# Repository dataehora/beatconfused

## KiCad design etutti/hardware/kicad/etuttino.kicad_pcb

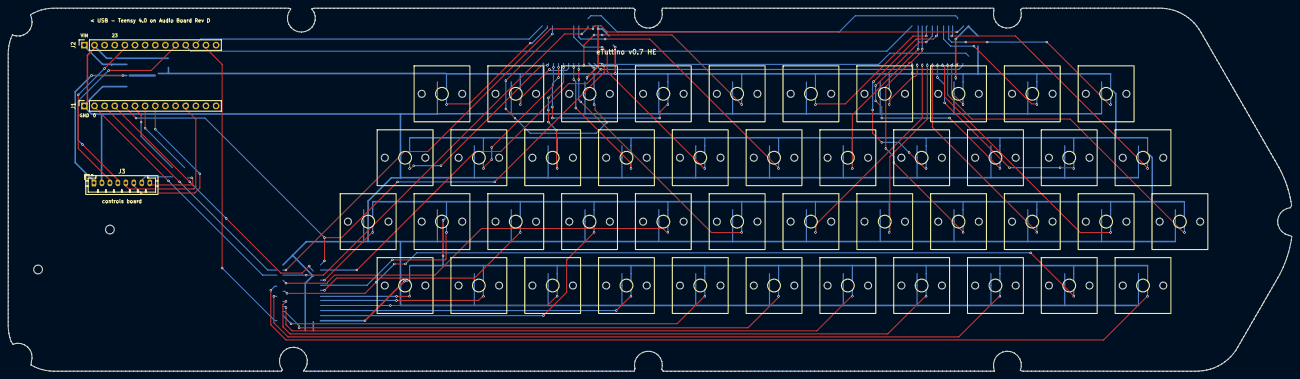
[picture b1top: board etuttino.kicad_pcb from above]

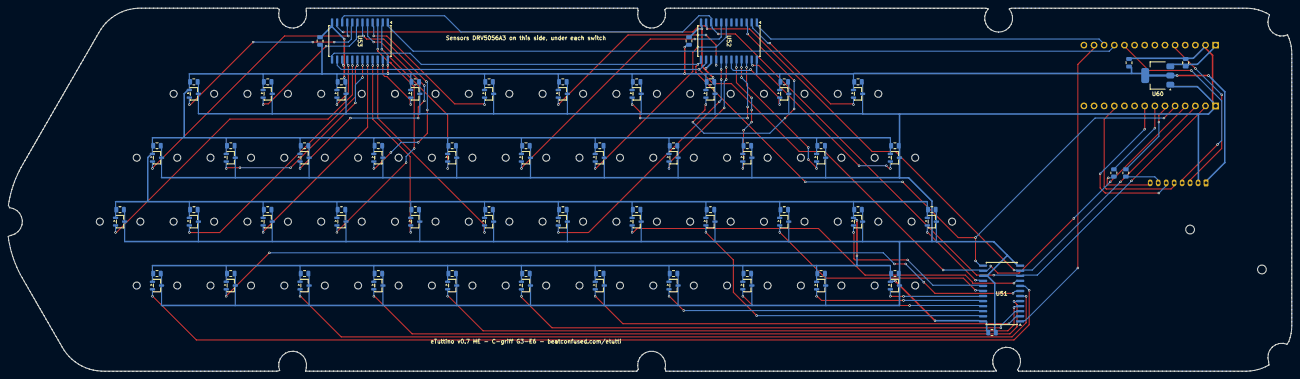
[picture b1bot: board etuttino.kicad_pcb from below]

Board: 2 copper layers, 321.8 x 91.0 mm, 148 parts (99 on the bottom side), 62 nets.

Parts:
C1, C2, C3, C4, C5, C6, C7, C8, C9, C10, C11, C12, C13, C14, C15, C16, C17, C18, C19, C20, C21, C22, C23, C24, C25, C26, C27, C28, C29, C30, C31, C32, C33, C34, C35, C36, C37, C38, C39, C40, C41, C42, C43, C44, C71, C72, C73: 100nF; C_0805_2012Metric
C80: 10uF; C_0805_2012Metric
C81: 22uF; C_0805_2012Metric
H1, H2: MountingHole_2.2mm_M2
J1, J2: PinSocket_1x14_P2.54mm_Vertical
J3: controls board; JST_PH_B8B-PH-K_1x08_P2.00mm_Vertical
R1, R2: 330; R_0805_2012Metric
SW1, SW2, SW3, SW4, SW5, SW6, SW7, SW8, SW9, SW10, SW11, SW12, SW13, SW14, SW15, SW16, SW17, SW18, SW19, SW20, SW21, SW22, SW23, SW24, SW25, SW26, SW27, SW28, SW29, SW30, SW31, SW32, SW33, SW34, SW35, SW36, SW37, SW38, SW39, SW40, SW41, SW42, SW43, SW44: Gateron_Magnetic_MX_1u
U1, U2, U3, U4, U5, U6, U7, U8, U9, U10, U11, U12, U13, U14, U15, U16, U17, U18, U19, U20, U21, U22, U23, U24, U25, U26, U27, U28, U29, U30, U31, U32, U33, U34, U35, U36, U37, U38, U39, U40, U41, U42, U43, U44: DRV5056A3QDBZR; SOT-23-3
U51, U52, U53: CD74HC4067M96; SOIC-24W_7.5x15.4mm_P1.27mm
U60: AMS1117-3.3; SOT-223-3_TabPin2

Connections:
COM0: J2.13, U51.1
COM1: J2.12, U52.1
COM2: J2.11, U53.1
ENC_A: J2.10, J3.4
ENC_B: J1.11, J3.5
ENC_SW: J1.8, J3.6
GND: C1.2, C2.2, C3.2, C4.2, C5.2, C6.2, C7.2, C8.2, C9.2, C10.2, C11.2, C12.2, C13.2, C14.2, C15.2, C16.2, C17.2, C18.2, C19.2, C20.2, C21.2, C22.2, C23.2, C24.2, C25.2, C26.2, C27.2, C28.2, C29.2, C30.2, C31.2, C32.2, C33.2, C34.2, C35.2, C36.2, C37.2, C38.2, C39.2, C40.2, C41.2, C42.2, C43.2, C44.2, C71.2, C72.1, C73.1, C80.1, C81.1, J1.1, J2.2, J3.2, U1.3, U2.3, U3.3, U4.3, U5.3, U6.3, U7.3, U8.3, U9.3, U10.3, U11.3, U12.3, U13.3, U14.3, U15.3, U16.3, U17.3, U18.3, U19.3, U20.3, U21.3, U22.3, U23.3, U24.3, U25.3, U26.3, U27.3, U28.3, U29.3, U30.3, U31.3, U32.3, U33.3, U34.3, U35.3, U36.3, U37.3, U38.3, U39.3, U40.3, U41.3, U42.3, U43.3, U44.3, U51.12, U51.15, U52.12, U52.15, U53.12, U53.15, U60.1
LED_G: J3.8, R2.2
LED_G_DRV: J1.7, R2.1
LED_R: J3.7, R1.2
LED_R_DRV: J1.6, R1.1
OUT_U1: U1.2, U51.19
OUT_U2: U2.2, U51.20
OUT_U3: U3.2, U51.21
OUT_U4: U4.2, U51.22
OUT_U5: U5.2, U51.2
OUT_U6: U6.2, U51.3
OUT_U7: U7.2, U51.4
OUT_U8: U8.2, U51.5
OUT_U9: U9.2, U51.6
OUT_U10: U10.2, U51.7
OUT_U11: U11.2, U51.8
OUT_U12: U12.2, U51.16
OUT_U13: U13.2, U51.17
OUT_U14: U14.2, U51.18
OUT_U15: U15.2, U51.23
OUT_U16: U16.2, U51.9
OUT_U17: U17.2, U52.17
OUT_U18: U18.2, U53.22
OUT_U19: U19.2, U53.21
OUT_U20: U20.2, U53.3
OUT_U21: U21.2, U53.20
OUT_U22: U22.2, U53.18
OUT_U23: U23.2, U53.17
OUT_U24: U24.2, U52.23
OUT_U25: U25.2, U52.22
OUT_U26: U26.2, U52.20
OUT_U27: U27.2, U52.18
OUT_U28: U28.2, U52.7
OUT_U29: U29.2, U52.8
OUT_U30: U30.2, U53.2
OUT_U31: U31.2, U53.6
OUT_U32: U32.2, U53.5
OUT_U33: U33.2, U53.19
OUT_U34: U34.2, U53.9
OUT_U35: U35.2, U52.2
OUT_U36: U36.2, U52.19
OUT_U37: U37.2, U52.3
OUT_U38: U38.2, U52.21
OUT_U39: U39.2, U52.16
OUT_U40: U40.2, U53.4
OUT_U41: U41.2, U53.23
OUT_U42: U42.2, U53.16
OUT_U43: U43.2, U53.7
OUT_U44: U44.2, U53.8
POT: J2.5, J3.3
SEL0: J1.2, U51.10, U52.10, U53.10
SEL1: J1.3, U51.11, U52.11, U53.11
SEL2: J1.4, U51.14, U52.14, U53.14
SEL3: J1.5, U51.13, U52.13, U53.13
VCC: C1.1, C2.1, C3.1, C4.1, C5.1, C6.1, C7.1, C8.1, C9.1, C10.1, C11.1, C12.1, C13.1, C14.1, C15.1, C16.1, C17.1, C18.1, C19.1, C20.1, C21.1, C22.1, C23.1, C24.1, C25.1, C26.1, C27.1, C28.1, C29.1, C30.1, C31.1, C32.1, C33.1, C34.1, C35.1, C36.1, C37.1, C38.1, C39.1, C40.1, C41.1, C42.1, C43.1, C44.1, C71.1, C72.2, C73.2, C81.2, J3.1, U1.1, U2.1, U3.1, U4.1, U5.1, U6.1, U7.1, U8.1, U9.1, U10.1, U11.1, U12.1, U13.1, U14.1, U15.1, U16.1, U17.1, U18.1, U19.1, U20.1, U21.1, U22.1, U23.1, U24.1, U25.1, U26.1, U27.1, U28.1, U29.1, U30.1, U31.1, U32.1, U33.1, U34.1, U35.1, U36.1, U37.1, U38.1, U39.1, U40.1, U41.1, U42.1, U43.1, U44.1, U51.24, U52.24, U53.24, U60.2
VIN: C80.2, J2.1, U60.3

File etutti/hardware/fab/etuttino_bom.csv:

Comment,Designator,Footprint,LCSC Part #
"DRV5056A3QDBZR","U1,U2,U3,U4,U5,U6,U7,U8,U9,U10,U11,U12,U13,U14,U15,U16,U17,U18,U19,U20,U21,U22,U23,U24,U25,U26,U27,U28,U29,U30,U31,U32,U33,U34,U35,U36,U37,U38,U39,U40,U41,U42,U43,U44","SOT-23-3",""
"100nF 0805 X7R","C1,C2,C3,C4,C5,C6,C7,C8,C9,C10,C11,C12,C13,C14,C15,C16,C17,C18,C19,C20,C21,C22,C23,C24,C25,C26,C27,C28,C29,C30,C31,C32,C33,C34,C35,C36,C37,C38,C39,C40,C41,C42,C43,C44,C71,C72,C73","C_0805","C49678"
"CD74HC4067M96","U51,U52,U53","SOIC-24W",""
"AMS1117-3.3","U60","SOT-223","C6186"
"10uF 0805","C80","C_0805","C15850"
"22uF 0805","C81","C_0805","C45783"
"330R 0805","R1,R2","R_0805","C17630"

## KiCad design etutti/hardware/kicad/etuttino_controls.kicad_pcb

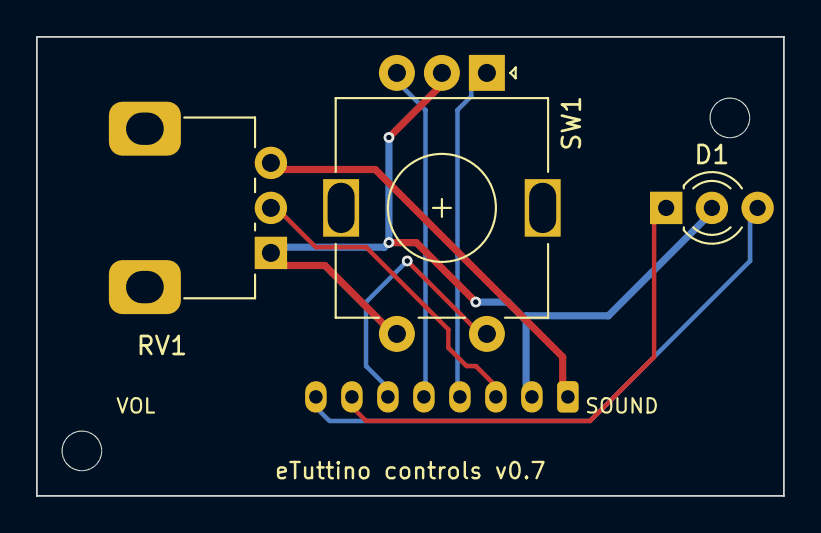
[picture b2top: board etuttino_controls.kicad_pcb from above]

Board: 2 copper layers, 41.5 x 25.5 mm, 6 parts (1 on the bottom side), 8 nets.

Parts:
D1: LED 3mm R/G CC; LED_D3.0mm-3
H1, H2: MountingHole_2.2mm_M2
J1: to main board J3; JST_PH_B8B-PH-K_1x08_P2.00mm_Vertical
RV1: RK09K 10k lin; Potentiometer_Alps_RK09K_Single_Vertical
SW1: EC11E; RotaryEncoder_Alps_EC11E-Switch_Vertical_H20mm

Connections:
ENC_A: J1.4, SW1.A
ENC_B: J1.5, SW1.B
ENC_SW: J1.6, SW1.S2
GND: D1.2, J1.2, RV1.1, SW1.C, SW1.S1
LED_G: D1.3, J1.8
LED_R: D1.1, J1.7
POT: J1.3, RV1.2
VCC: J1.1, RV1.3

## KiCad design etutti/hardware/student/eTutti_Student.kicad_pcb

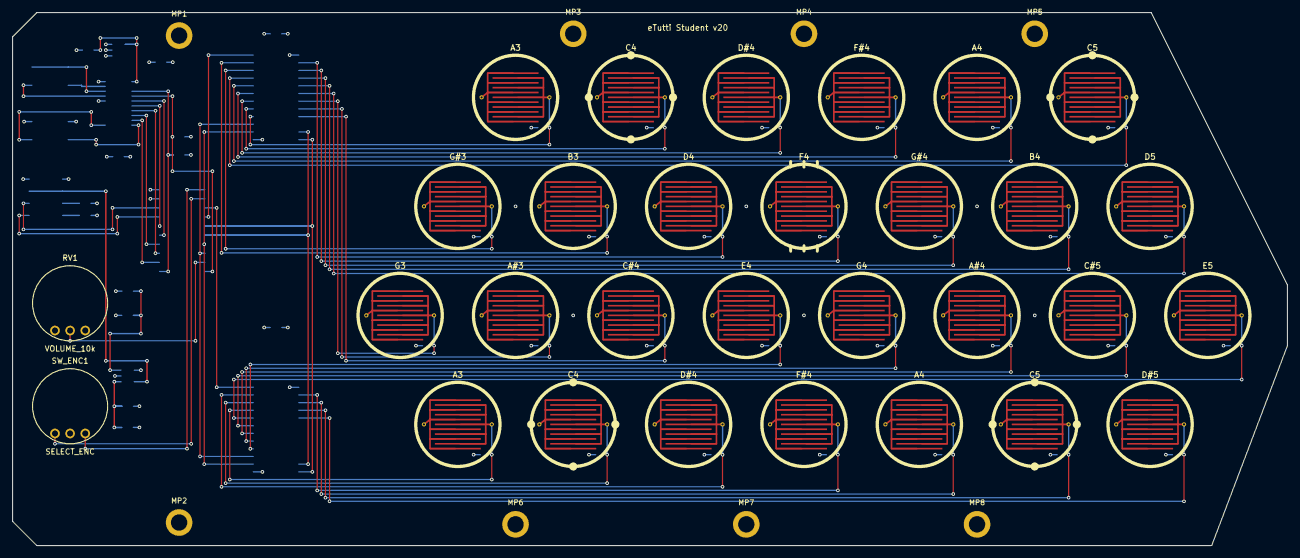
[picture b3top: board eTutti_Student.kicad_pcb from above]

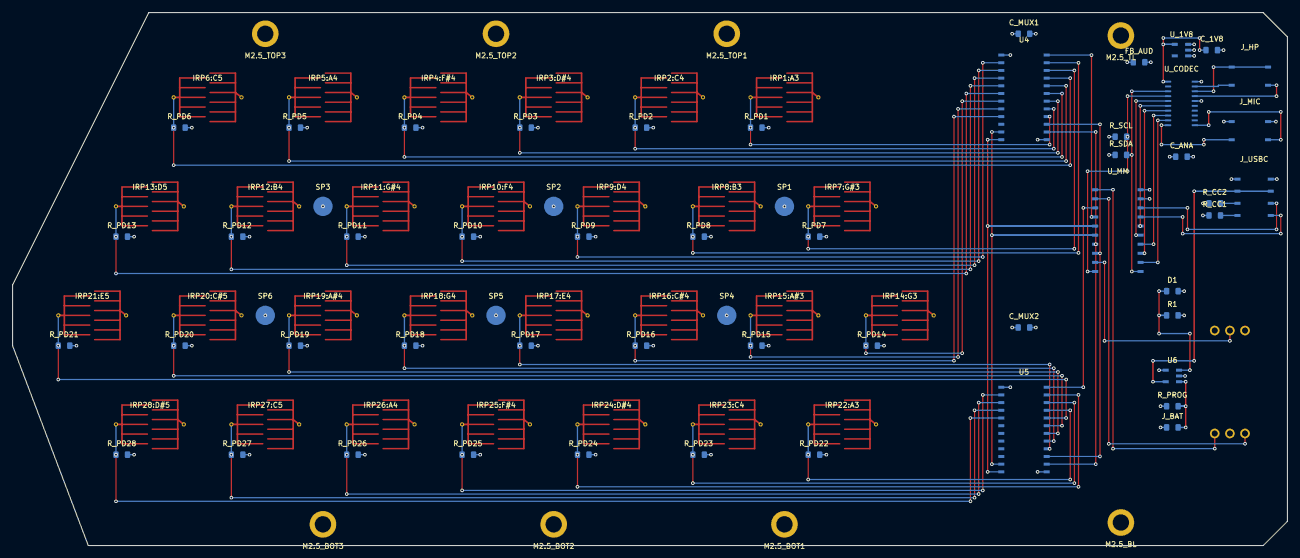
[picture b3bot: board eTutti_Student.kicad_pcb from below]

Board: 4 copper layers, 210.5 x 88.0 mm, 94 parts (56 on the bottom side), 60 nets.

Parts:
C_1V8: 100nF; SMD_0805_C_1V8
C_ANA: 10uF; SMD_0805_C_ANA
C_MUX1: 100nF; SMD_0805_C_MUX1
C_MUX2: 100nF; SMD_0805_C_MUX2
D1: LED_STATUS; SMD_0805_D1
FB_AUD: FERRITE; SMD_0805_FB_AUD
IRP1, IRP22: A3; IRP_14mm_Tactile
IRP2, IRP23: C4; IRP_14mm_Tactile
IRP3, IRP24: D#4; IRP_14mm_Tactile
IRP4, IRP25: F#4; IRP_14mm_Tactile
IRP5, IRP26: A4; IRP_14mm_Tactile
IRP6, IRP27: C5; IRP_14mm_Tactile
IRP7: G#3; IRP_14mm_Tactile
IRP8: B3; IRP_14mm_Tactile
IRP9: D4; IRP_14mm_Tactile
IRP10: F4; IRP_14mm_Tactile
IRP11: G#4; IRP_14mm_Tactile
IRP12: B4; IRP_14mm_Tactile
IRP13: D5; IRP_14mm_Tactile
IRP14: G3; IRP_14mm_Tactile
IRP15: A#3; IRP_14mm_Tactile
IRP16: C#4; IRP_14mm_Tactile
IRP17: E4; IRP_14mm_Tactile
IRP18: G4; IRP_14mm_Tactile
IRP19: A#4; IRP_14mm_Tactile
IRP20: C#5; IRP_14mm_Tactile
IRP21: E5; IRP_14mm_Tactile
IRP28: D#5; IRP_14mm_Tactile
J_BAT: BATT_JST; SMD_0805_J_BAT
J_HP: PHONES_3.5mm; J_HP_Back
J_MIC: MIC_IN_3.5mm; J_MIC_Back
J_USBC: USB-C_PORT; J_USBC_Back
MP1: M2.5_TL; MountingHole_M2.5_Pad
MP2: M2.5_BL; MountingHole_M2.5_Pad
MP3: M2.5_TOP1; MountingHole_M2.5_Pad
MP4: M2.5_TOP2; MountingHole_M2.5_Pad
MP5: M2.5_TOP3; MountingHole_M2.5_Pad
MP6: M2.5_BOT1; MountingHole_M2.5_Pad
MP7: M2.5_BOT2; MountingHole_M2.5_Pad
MP8: M2.5_BOT3; MountingHole_M2.5_Pad
R1: 330R; SMD_0805_R1
RV1: VOLUME_10k; RV1_Top
R_CC1: 5.1k; SMD_0805_R_CC1
R_CC2: 5.1k; SMD_0805_R_CC2
R_PD1: 10k; SMD_0805_R_PD1
R_PD2: 10k; SMD_0805_R_PD2
R_PD3: 10k; SMD_0805_R_PD3
R_PD4: 10k; SMD_0805_R_PD4
R_PD5: 10k; SMD_0805_R_PD5
R_PD6: 10k; SMD_0805_R_PD6
R_PD7: 10k; SMD_0805_R_PD7
R_PD8: 10k; SMD_0805_R_PD8
R_PD9: 10k; SMD_0805_R_PD9
R_PD10: 10k; SMD_0805_R_PD10
R_PD11: 10k; SMD_0805_R_PD11
R_PD12: 10k; SMD_0805_R_PD12
R_PD13: 10k; SMD_0805_R_PD13
R_PD14: 10k; SMD_0805_R_PD14
R_PD15: 10k; SMD_0805_R_PD15
R_PD16: 10k; SMD_0805_R_PD16
R_PD17: 10k; SMD_0805_R_PD17
R_PD18: 10k; SMD_0805_R_PD18
R_PD19: 10k; SMD_0805_R_PD19
R_PD20: 10k; SMD_0805_R_PD20
R_PD21: 10k; SMD_0805_R_PD21
R_PD22: 10k; SMD_0805_R_PD22
R_PD23: 10k; SMD_0805_R_PD23
R_PD24: 10k; SMD_0805_R_PD24
R_PD25: 10k; SMD_0805_R_PD25
R_PD26: 10k; SMD_0805_R_PD26
R_PD27: 10k; SMD_0805_R_PD27
R_PD28: 10k; SMD_0805_R_PD28
R_PROG: 2k_PROG; SMD_0805_R_PROG
R_SCL: 2.2k; SMD_0805_R_SCL
R_SDA: 2.2k; SMD_0805_R_SDA
SP1: RIB_SUP_1; Back_Support_Pillar_M2.5
SP2: RIB_SUP_2; Back_Support_Pillar_M2.5
SP3: RIB_SUP_3; Back_Support_Pillar_M2.5
SP4: RIB_SUP_4; Back_Support_Pillar_M2.5
SP5: RIB_SUP_5; Back_Support_Pillar_M2.5
SP6: RIB_SUP_6; Back_Support_Pillar_M2.5
SW_ENC1: SELECT_ENC; SW_ENC1_Top
U4: MUX_1-16_HC4067; U4_Back
U5: MUX_17-28_HC4067; U5_Back
U6: MCP73831_CHG; SOT23_5_U6
U_1V8: 1.8V_LDO; SOT23_5_U_1V8
U_CODEC: SGTL5000; U_CODEC_Back
U_MM: TEENSY_MICROMOD; U_MM_Back

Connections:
+1V8_CODEC: C_1V8.2, U_1V8.5, U_CODEC.20
+3V3: C_MUX1.1, C_MUX2.1, FB_AUD.2, IRP1.1, IRP2.1, IRP3.1, IRP4.1, IRP5.1, IRP6.1, IRP7.1, IRP8.1, IRP9.1, IRP10.1, IRP11.1, IRP12.1, IRP13.1, IRP14.1, IRP15.1, IRP16.1, IRP17.1, IRP18.1, IRP19.1, IRP20.1, IRP21.1, IRP22.1, IRP23.1, IRP24.1, IRP25.1, IRP26.1, IRP27.1, IRP28.1, R1.1, RV1.3, R_SCL.2, R_SDA.2, U4.24, U5.24, U_MM.2
+3V3_ANA: C_ANA.1, FB_AUD.1, U_1V8.1, U_1V8.3, U_CODEC.5
+5V_USB: J_USBC.2, J_USBC.7, U6.4
+VBAT: J_BAT.1, R_PROG.1, U6.3
ENC_A: SW_ENC1.1, U_MM.19
ENC_B: SW_ENC1.3, U_MM.20
GND: C_1V8.1, C_ANA.2, C_MUX1.2, C_MUX2.2, D1.1, J_BAT.2, J_MIC.1, J_MIC.4, J_USBC.1, J_USBC.8, MP1.1, MP2.1, MP3.1, MP4.1, MP5.1, MP6.1, MP7.1, MP8.1, RV1.1, R_CC1.2, R_CC2.2, R_PD1.1, R_PD2.1, R_PD3.1, R_PD4.1, R_PD5.1, R_PD6.1, R_PD7.1, R_PD8.1, R_PD9.1, R_PD10.1, R_PD11.1, R_PD12.1, R_PD13.1, R_PD14.1, R_PD15.1, R_PD16.1, R_PD17.1, R_PD18.1, R_PD19.1, R_PD20.1, R_PD21.1, R_PD22.1, R_PD23.1, R_PD24.1, R_PD25.1, R_PD26.1, R_PD27.1, R_PD28.1, R_PROG.2, SP1.1, SP2.1, SP3.1, SP4.1, SP5.1, SP6.1, SW_ENC1.2, U4.12, U5.12, U6.2, U6.5, U_1V8.2, U_CODEC.1, U_MM.1
HP_L: J_HP.2, U_CODEC.4
HP_R: J_HP.3, U_CODEC.2
HP_VGND: J_HP.1, J_HP.4, U_CODEC.3
I2C_SCL: R_SCL.1, U_CODEC.17, U_MM.11
I2C_SDA: R_SDA.1, U_CODEC.18, U_MM.10
I2S_BCLK: U_CODEC.14, U_MM.8
I2S_LRCLK: U_CODEC.13, U_MM.7
I2S_MCLK: U_CODEC.12, U_MM.9
I2S_RX: U_CODEC.16, U_MM.6
I2S_TX: U_CODEC.15, U_MM.5
KEY_SIG_1: IRP1.2, R_PD1.2, U4.9
KEY_SIG_2: IRP2.2, R_PD2.2, U4.8
KEY_SIG_3: IRP3.2, R_PD3.2, U4.7
KEY_SIG_4: IRP4.2, R_PD4.2, U4.6
KEY_SIG_5: IRP5.2, R_PD5.2, U4.5
KEY_SIG_6: IRP6.2, R_PD6.2, U4.4
KEY_SIG_7: IRP7.2, R_PD7.2, U4.3
KEY_SIG_8: IRP8.2, R_PD8.2, U4.2
KEY_SIG_9: IRP9.2, R_PD9.2, U4.23
KEY_SIG_10: IRP10.2, R_PD10.2, U4.22
KEY_SIG_11: IRP11.2, R_PD11.2, U4.21
KEY_SIG_12: IRP12.2, R_PD12.2, U4.20
KEY_SIG_13: IRP13.2, R_PD13.2, U4.19
KEY_SIG_14: IRP14.2, R_PD14.2, U4.18
KEY_SIG_15: IRP15.2, R_PD15.2, U4.17
KEY_SIG_16: IRP16.2, R_PD16.2, U4.16
KEY_SIG_17: IRP17.2, R_PD17.2, U5.9
KEY_SIG_18: IRP18.2, R_PD18.2, U5.8
KEY_SIG_19: IRP19.2, R_PD19.2, U5.7
KEY_SIG_20: IRP20.2, R_PD20.2, U5.6
KEY_SIG_21: IRP21.2, R_PD21.2, U5.5
KEY_SIG_22: IRP22.2, R_PD22.2, U5.4
KEY_SIG_23: IRP23.2, R_PD23.2, U5.3
KEY_SIG_24: IRP24.2, R_PD24.2, U5.2
KEY_SIG_25: IRP25.2, R_PD25.2, U5.23
KEY_SIG_26: IRP26.2, R_PD26.2, U5.22
KEY_SIG_27: IRP27.2, R_PD27.2, U5.21
KEY_SIG_28: IRP28.2, R_PD28.2, U5.20
MIC_BIAS: J_MIC.3, U_CODEC.11
MIC_IN: J_MIC.2, U_CODEC.10
MUX1_OUT: U4.1, U_MM.17
MUX2_OUT: U5.1, U_MM.18
MUX_S0: U4.10, U5.10, U_MM.13
MUX_S1: U4.11, U5.11, U_MM.14
MUX_S2: U4.14, U5.14, U_MM.15
MUX_S3: U4.13, U5.13, U_MM.16
USB_CC1: J_USBC.5, R_CC1.1
USB_CC2: J_USBC.6, R_CC2.1
USB_D_N: J_USBC.4, U_MM.4
USB_D_P: J_USBC.3, U_MM.3
USER_LED: D1.2, R1.2, U6.1
VOL_ADC: RV1.2, U_MM.12

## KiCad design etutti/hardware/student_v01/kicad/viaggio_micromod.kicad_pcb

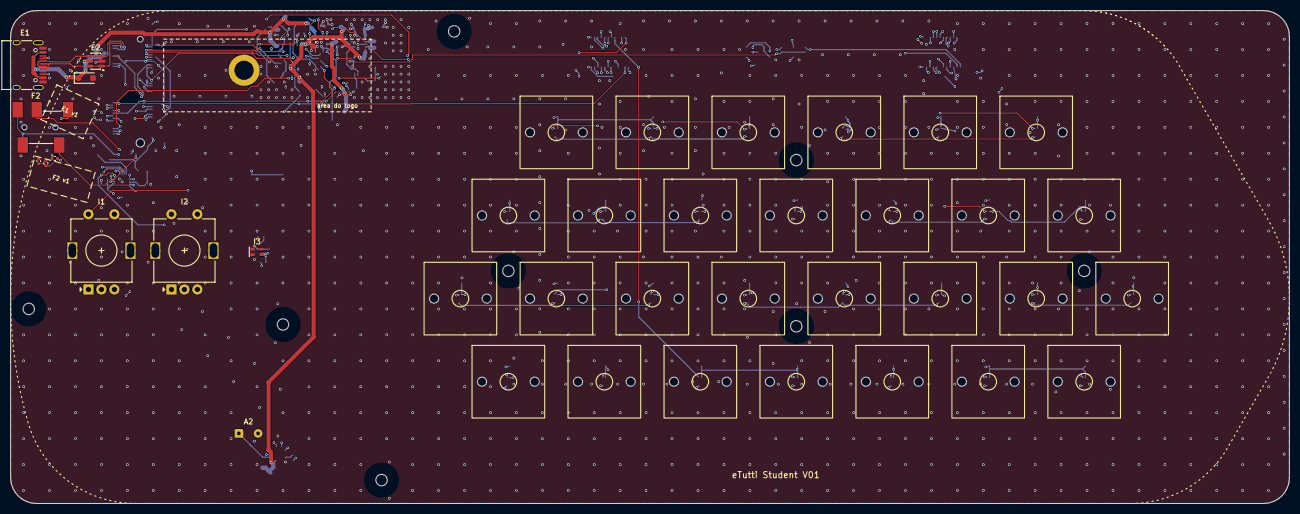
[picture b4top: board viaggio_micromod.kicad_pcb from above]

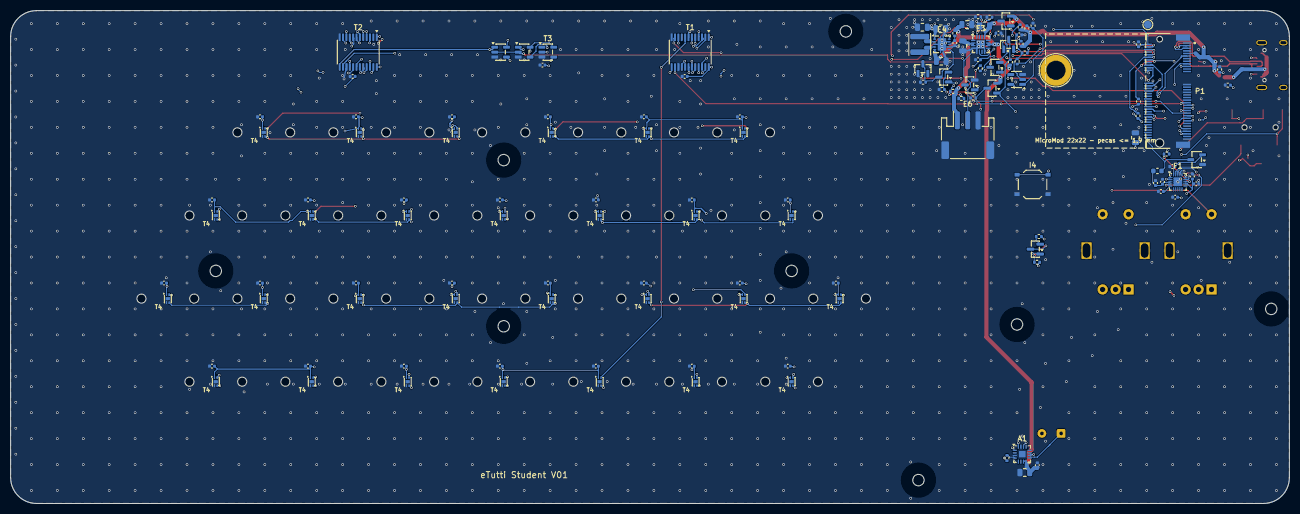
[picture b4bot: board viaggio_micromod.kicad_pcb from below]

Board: 4 copper layers, 246.5 x 95.0 mm, 178 parts (130 on the bottom side), 99 nets.

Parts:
C101, C201, C202, C203, C206, C207, C208, C501: 10uF; C_0805_2012Metric
C102, C204, C205, C209, C302, C304, C305, C308, C502, C601, C602, C603, C701, C702, C703, C704, C705, C706, C707, C708, C709, C710, C711, C712, C713, C714, C715, C716, C717, C718, C719, C720, C721, C722, C723, C724, C725, C726, C727, C728: 100nF; C_0402_1005Metric
C210: 10uF; C_0603_1608Metric
C213: 1uF; C_0402_1005Metric
C301, C303, C306: 2.2uF; C_0402_1005Metric
C307: 150nF; C_0402_1005Metric
D201: SMF5.0A; D_SOD-123F
D202, D203, D204, D205, D402: BAT54C; SOT-23
D401: TJ-S1615SW6TGLCRG-A5; LED_1615_RG_4pad
FB301: 600R@100MHz; L_0603_1608Metric
H1, H2, H3, H4, H5, H6, H7, H8: MountingHole_2.2mm_M2
H101: 9774025151R; Standoff_SMD_M2.5_H2.5
J101: 91302-42-067RCE; M.2_E_H4.2_UMAX_91302-42-067
J201: TYPE-C-31-M-12; USB_C_Receptacle_HRO_TYPE-C-31-M-12
J202: S3B-PH-SM4-TB; JST_PH_S3B-PH-SM4-TB_1x03-1MP_P2.00mm_Horizontal
J301: PJ-327A 5JJ; Jack_3.5mm_PJ-327A_SMD
J501: alto-falante (fios); SolderWire-0.127sqmm_1x02_P3.7mm_D0.48mm_OD1mm
L201: 2.2uH; L_Changjiang_FNR4020S
Q201, Q203: AO3401A; SOT-23
Q202: AO3400A; SOT-23
R105, R216: 100; R_0402_1005Metric
R201, R202: 5.1k; R_0402_1005Metric
R203: 1.8k; R_0402_1005Metric
R204: 1.5k; R_0402_1005Metric
R205, R214: 10k; R_0402_1005Metric
R206, R210, R211, R213, R215, R218, R303: 100k; R_0402_1005Metric
R207, R217: 1k; R_0402_1005Metric
R208, R209, R212, R304: 1M; R_0402_1005Metric
R301, R302: 2.2k; R_0402_1005Metric
R401: 270; R_0402_1005Metric
R402: 330; R_0402_1005Metric
R501: 680k; R_0402_1005Metric
SW1, SW2, SW3, SW4, SW5, SW6, SW7, SW8, SW9, SW10, SW11, SW12, SW13, SW14, SW15, SW16, SW17, SW18, SW19, SW20, SW21, SW22, SW23, SW24, SW25, SW26, SW27, SW28: Gateron_Magnetic_MX_1u
SW401, SW402: EC11E18244A5; RotaryEncoder_Alps_EC11E-Switch_Vertical_H20mm
SW403: Program; SW_Push_1P1T_XKB_TS-1187A
TP101: RESET#/ONOFF; TestPoint_Pad_D1.5mm
U201: USBLC6-2SC6; SOT-23-6
U202: BQ24074RGTR; VQFN-16-1EP_3x3mm_P0.5mm_EP1.6x1.6mm
U203, U604, U605: 74LVC1G08; SOT-23-5
U204: TPS63001DRCR; Texas_DRC0010J
U301: SGTL5000XNLA3; QFN-20-1EP_3x3mm_P0.4mm_EP1.65x1.65mm
U302: XC6206P182MR; SOT-23-3
U501: MAX98357AETE+T; TQFN-16-1EP_3x3mm_P0.5mm_EP1.23x1.23mm
U601, U602: 74HC4067PW; TSSOP-24_4.4x7.8mm_P0.65mm
U603: 74LVC1G04; SOT-23-5
U701, U702, U703, U704, U705, U706, U707, U708, U709, U710, U711, U712, U713, U714, U715, U716, U717, U718, U719, U720, U721, U722, U723, U724, U725, U726, U727, U728: TMAG5253BA3IQDMRR; Texas_X2SON-4-1EP_1.1x1.4mm_P0.5mm_EP0.8x0.6mm

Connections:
+3V3: C101.1, C102.1, C205.1, C207.1, C208.1, C303.1, C304.1, C305.1, C601.1, C602.1, C603.1, C701.1, C702.1, C703.1, C704.1, C705.1, C706.1, C707.1, C708.1, C709.1, C710.1, C711.1, C712.1, C713.1, C714.1, C715.1, C716.1, C717.1, C718.1, C719.1, C720.1, C721.1, C722.1, C723.1, C724.1, C725.1, C726.1, C727.1, C728.1, FB301.1, J101.2, J101.74, Q202.1, R218.1, R301.1, R302.1, U203.5, U204.1, U204.10, U301.12, U302.3, U601.24, U602.24, U603.5, U604.5, U605.5, U701.1, U702.1, U703.1, U704.1, U705.1, U706.1, U707.1, U708.1, U709.1, U710.1, U711.1, U712.1, U713.1, U714.1, U715.1, U716.1, U717.1, U718.1, U719.1, U720.1, U721.1, U722.1, U723.1, U724.1, U725.1, U726.1, U727.1, U728.1
AMP_SD: J101.61, R501.1
AMP_SDM: R501.2, U501.4
AUD_MCLK: R105.2, U301.13
AUD_MCLK_P: J101.58, R105.1
BAT_NTC: J202.2, U202.1
BB_L1: L201.1, U204.4
BB_L2: L201.2, U204.2
BB_VINA: C209.1, R216.2, U204.8
CC1: J201.A5, R201.1
CC2: J201.B5, R202.1
CHGA: D402.1, Q202.3, R207.2
CHGLED: Q201.3, R207.1
CHG_EN1: R205.2, U202.6
CHG_ILIM: R204.1, U202.12
CHG_ISET: R203.1, U202.16
CHG_N: D202.3, Q201.1, R206.2, U202.9
CHG_STAT: D202.1, J101.67
EN_A: U604.4, U701.3, U702.3, U703.3, U704.3, U705.3, U706.3, U707.3, U716.3, U717.3, U718.3, U719.3, U720.3, U721.3, U722.3
EN_B: U605.4, U708.3, U709.3, U710.3, U711.3, U712.3, U713.3, U714.3, U715.3, U723.3, U724.3, U725.3, U726.3, U727.3, U728.3
EN_REQ: D203.3, D204.3, R212.1, U204.6
GND: C101.2, C102.2, C201.2, C202.2, C203.2, C204.2, C205.2, C206.2, C207.2, C208.2, C209.2, C210.2, C213.2, C301.2, C302.2, C303.2, C304.2, C305.2, C306.2, C307.2, C308.2, C501.2, C502.2, C601.2, C602.2, C603.2, C701.2, C702.2, C703.2, C704.2, C705.2, C706.2, C707.2, C708.2, C709.2, C710.2, C711.2, C712.2, C713.2, C714.2, C715.2, C716.2, C717.2, C718.2, C719.2, C720.2, C721.2, C722.2, C723.2, C724.2, C725.2, C726.2, C727.2, C728.2, D201.2, D401.2, D401.4, H101.1, J101.1, J101.7, J101.33, J101.36, J101.39, J101.45, J101.75, J101.MP, J201.A1, J201.A12, J201.B1, J201.B12, J201.SH, J202.3, J202.MP, Q202.2, R201.2, R202.2, R203.2, R204.2, R209.2, R211.2, R212.2, R213.2, R215.2, R304.2, SW401.C, SW401.MP, SW401.S1, SW402.C, SW402.MP, SW402.S1, SW403.2, U201.2, U202.4, U202.5, U202.8, U202.17, U203.3, U204.3, U204.7, U204.9, U204.11, U301.21, U302.1, U501.3, U501.11, U501.15, U501.17, U601.12, U601.15, U602.12, U602.15, U603.3, U604.3, U605.3, U701.2, U701.5, U702.2, U702.5, U703.2, U703.5, U704.2, U704.5, U705.2, U705.5, U706.2, U706.5, U707.2, U707.5, U708.2, U708.5, U709.2, U709.5, U710.2, U710.5, U711.2, U711.5, U712.2, U712.5, U713.2, U713.5, U714.2, U714.5, U715.2, U715.5, U716.2, U716.5, U717.2, U717.5, U718.2, U718.5, U719.2, U719.5, U720.2, U720.5, U721.2, U721.5, U722.2, U722.5, U723.2, U723.5, U724.2, U724.5, U725.2, U725.5, U726.2, U726.5, U727.2, U727.5, U728.2, U728.5
HP_DET: C308.1, J101.22, R303.2, R304.1
HP_L: J301.4, U301.4
HP_R: J301.3, U301.1
HP_TIPSW: J301.5, R303.1
HP_VGND: J301.1, J301.2, U301.2
I2C_SCL: J101.14, R302.2, U301.19
I2C_SDA: J101.12, R301.2, U301.18
I2S_BCLK: J101.50, U301.15, U501.16
I2S_LRCLK: J101.52, U301.14, U501.14
I2S_TX: J101.56, U301.17, U501.1
KEEP: D203.2, J101.55, R213.1
LEDR_A: D402.2, R401.2
LED_G: J101.18, R402.1
LED_G_A: D401.3, R402.2
LED_R: J101.57, R401.1
LED_R_A: D401.1, D402.3
MUX_L_COM: J101.38, U601.1
MUX_R_COM: J101.34, U602.1
MUX_S0: J101.19, U601.10, U602.10
MUX_S1: J101.17, U601.11, U602.11
MUX_S2: J101.47, U601.14, U602.14
MUX_S3: J101.32, U601.13, U602.13, U603.2, U605.1
NS3: U603.4, U604.1
ONOFF: D205.2, J101.6, TP101.1
OUT_K01: U601.4, U701.4
OUT_K02: U601.5, U702.4
OUT_K03: U601.8, U703.4
OUT_K04: U601.6, U704.4
OUT_K05: U602.7, U705.4
OUT_K06: U602.8, U706.4
OUT_K07: U602.9, U707.4
OUT_K08: U601.22, U708.4
OUT_K09: U601.21, U709.4
OUT_K10: U601.16, U710.4
OUT_K11: U601.18, U711.4
OUT_K12: U602.18, U712.4
OUT_K13: U602.20, U713.4
OUT_K14: U602.17, U714.4
OUT_K15: U602.16, U715.4
OUT_K16: U601.7, U716.4
OUT_K17: U601.2, U717.4
OUT_K18: U601.3, U718.4
OUT_K19: U602.5, U719.4
OUT_K20: U602.3, U720.4
OUT_K21: U602.4, U721.4
OUT_K22: U602.6, U722.4
OUT_K23: U601.19, U723.4
OUT_K24: U601.20, U724.4
OUT_K25: U601.23, U725.4
OUT_K26: U602.22, U726.4
OUT_K27: U602.23, U727.4
OUT_K28: U602.21, U728.4
PROG: J101.11, SW403.1
PWR_EN: J101.4, R217.1
PWR_EN_S: C213.1, R217.2, R218.2, U203.2
PWR_KEY: D203.1, Q203.3, R211.1
SEL_A: J101.59, SW402.A
SEL_B: J101.69, SW402.B
SEL_SW: J101.71, SW402.S2
SENS_EN: J101.10, U604.2, U605.2
SGTL_VAG: C307.1, U301.5
SGTL_VDDA: C301.1, C302.1, FB301.2, U301.3
SGTL_VDDD: C306.1, U301.20, U302.2
SPK_N: J501.2, U501.10
SPK_P: J501.1, U501.9
USB_DN: J101.5, J201.A7, J201.B7, U201.3, U201.4
USB_DP: J101.3, J201.A6, J201.B6, U201.1, U201.6
USB_HOLD: D204.1, U203.4
VBAT: C203.1, J202.1, R208.1, U202.2, U202.3
VBAT_S: C204.1, J101.20, R208.2, R209.1
VBUS: C201.1, D201.1, J101.9, J201.A4, J201.A9, J201.B4, J201.B9, Q201.2, R205.1, R206.1, R214.1, U201.5, U202.13
VBUS_S: R214.2, R215.1, U203.1
VOL_A: J101.49, SW401.A
VOL_B: J101.53, SW401.B
VOL_SW: D205.1, J101.51
VOL_SW_N: D205.3, Q203.1, R210.2, SW401.S2
VSYS: C202.1, C206.1, C210.1, C501.1, C502.1, Q203.2, R210.1, R216.1, U202.10, U202.11, U204.5, U501.7, U501.8

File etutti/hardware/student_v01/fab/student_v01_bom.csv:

Comment,Designator,Footprint,LCSC Part #
100nF,"C102,C204,C205,C209,C302,C304,C305,C308,C502,C601,C602,C603,C701,C702,C703,C704,C705,C706,C707,C708,C709,C710,C711,C712,C713,C714,C715,C716,C717,C718,C719,C720,C721,C722,C723,C724,C725,C726,C727,C728",C_0402_1005Metric,C1525
1uF,C213,C_0402_1005Metric,C52923
2.2uF,"C301,C303,C306",C_0402_1005Metric,C12530
150nF,C307,C_0402_1005Metric,C162182
10uF,C210,C_0603_1608Metric,C19702
10uF,"C101,C201,C202,C203,C206,C207,C208,C501",C_0805_2012Metric,C15850
SMF5.0A,D201,D_SOD-123F,C151296
S3B-PH-SM4-TB,J202,JST_PH_S3B-PH-SM4-TB_1x03-1MP_P2.00mm_Horizontal,C265101
PJ-327A 5JJ,J301,Jack_3.5mm_PJ-327A_SMD,C668605
TJ-S1615SW6TGLCRG-A5,D401,LED_1615_RG_4pad,C273605
600R@100MHz,FB301,L_0603_1608Metric,C1002
2.2uH,L201,L_Changjiang_FNR4020S,C167825
91302-42-067RCE,J101,M.2_E_H4.2_UMAX_91302-42-067,C48985906
SGTL5000XNLA3,U301,QFN-20-1EP_3x3mm_P0.4mm_EP1.65x1.65mm,C2651833
100,"R105,R216",R_0402_1005Metric,C25076
5.1k,"R201,R202",R_0402_1005Metric,C25905
1.8k,R203,R_0402_1005Metric,C25871
1.5k,R204,R_0402_1005Metric,C25867
10k,"R205,R214",R_0402_1005Metric,C25744
100k,"R206,R210,R211,R213,R215,R218,R303",R_0402_1005Metric,C25741
1k,"R207,R217",R_0402_1005Metric,C11702
1M,"R208,R209,R212,R304",R_0402_1005Metric,C26083
2.2k,"R301,R302",R_0402_1005Metric,C25879
270,R401,R_0402_1005Metric,C25099
330,R402,R_0402_1005Metric,C25104
680k,R501,R_0402_1005Metric,C4131
EC11E18244A5,"SW401,SW402",RotaryEncoder_Alps_EC11E-Switch_Vertical_H20mm,C255515
BAT54C,"D202,D203,D204,D205,D402",SOT-23,C134405
AO3401A,"Q201,Q203",SOT-23,C15127
AO3400A,Q202,SOT-23,C20917
XC6206P182MR,U302,SOT-23-3,C347373
74LVC1G08,"U203,U604,U605",SOT-23-5,C7666
74LVC1G04,U603,SOT-23-5,C7827
USBLC6-2SC6,U201,SOT-23-6,C7519
Program,SW403,SW_Push_1P1T_XKB_TS-1187A,C318884
9774025151R,H101,Standoff_SMD_M2.5_H2.5,C7496631
MAX98357AETE+T,U501,TQFN-16-1EP_3x3mm_P0.5mm_EP1.23x1.23mm,C910544
74HC4067PW,"U601,U602",TSSOP-24_4.4x7.8mm_P0.65mm,C179326
TPS63001DRCR,U204,Texas_DRC0010J,C28060
TMAG5253BA3IQDMRR,"U701,U702,U703,U704,U705,U706,U707,U708,U709,U710,U711,U712,U713,U714,U715,U716,U717,U718,U719,U720,U721,U722,U723,U724,U725,U726,U727,U728",Texas_X2SON-4-1EP_1.1x1.4mm_P0.5mm_EP0.8x0.6mm,C22401868
TYPE-C-31-M-12,J201,USB_C_Receptacle_HRO_TYPE-C-31-M-12,C165948
BQ24074RGTR,U202,VQFN-16-1EP_3x3mm_P0.5mm_EP1.6x1.6mm,C54313

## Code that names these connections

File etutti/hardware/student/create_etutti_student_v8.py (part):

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    p_ucod20 = PAD_COORDS[("U_CODEC", "20")][:2]
    add_poly_route([p_c1v8, (14.45, 5.0), (20.1, 5.0), p_u1v8, (22.2, 5.55), (22.2, p_ucod20[1]), p_ucod20], "+1V8_CODEC", "B.Cu", 0.25)

    # Headphone Out: HP_R (Pin 2), HP_VGND (Pin 3), HP_L (Pin 4)
    p_jhp1 = PAD_COORDS[("J_HP", "1")][:2]
    p_jhp2 = PAD_COORDS[("J_HP", "2")][:2]
    p_jhp3 = PAD_COORDS[("J_HP", "3")][:2]
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    add_poly_route([p_jhp3, (12.2, 12.0), (12.2, p_cod2[1]), p_cod2], "HP_R", "B.Cu", 0.25)
    add_poly_route([p_jhp2, (2.8, 13.8), (14.2, 13.8), (14.2, p_cod4[1]), p_cod4], "HP_L", "B.Cu", 0.25)

    # Microphone In: MIC_IN (Pin 10), MIC_BIAS (Pin 11)
    p_jmic2 = PAD_COORDS[("J_MIC", "2")][:2]
    p_jmic3 = PAD_COORDS[("J_MIC", "3")][:2]
    p_cod10 = PAD_COORDS[("U_CODEC", "10")][:2]
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
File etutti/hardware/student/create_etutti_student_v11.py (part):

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    route_2layer_clean(p_c1v8[0], p_c1v8[1], p_u1v8[0], p_u1v8[1], 14.5, "+1V8_CODEC", 0.22)
    route_2layer_clean(p_u1v8[0], p_u1v8[1], p_ucod20[0], p_ucod20[1], 20.5, "+1V8_CODEC", 0.22)

    # J_HP Pad 1 (-3.0, 9.0) & Pad 4 (+3.0, 9.0) are BOTH HP_VGND -> connect them directly at Y=9.0, then route to U_CODEC Pin 3!
    p_jhp1 = PAD_COORDS[("J_HP", "1")][:2]
    p_jhp2 = PAD_COORDS[("J_HP", "2")][:2]
    p_jhp3 = PAD_COORDS[("J_HP", "3")][:2]
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    route_2layer_clean(p_jmic2[0], p_jmic2[1], 13.0, 18.6, 1.2, "MIC_IN", 0.22)
    add_seg(13.0, 18.6, p_cod10[0], p_cod10[1], "MIC_IN", "B.Cu", 0.22)

    # MIC_BIAS from J_MIC Pad 3 (9.2, 21.0) to U_CODEC Pin 11 (19.7, 18.6) via Y=21.8 dogleg so it doesn't share Y=18.6 with MIC_IN!
    route_2layer_clean(p_jmic3[0], p_jmic3[1], 20.8, 21.8, 13.8, "MIC_BIAS", 0.22)
    route_2layer_clean(20.8, 21.8, p_cod11[0], p_cod11[1], 20.8, "MIC_BIAS", 0.22)

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        route_2layer_clean(pu4[0], pu4[1], pmm[0], pmm[1], gx_top, net_n, 0.20)
        route_2layer_clean(pmm[0], pmm[1], pu5[0], pu5[1], gx_bot, net_n, 0.20)

    # MUX_S2 & MUX_S3 (Right side of U_MM -> step via Y=44.5 / 45.2 corridor to Right side of U4/U5 so they never cross U4 Pin 10/11!)
    for net_n, mm_pin, mux_pin, gx_mm, hy_mid, gx_mux in [
        ("MUX_S2", "15", "14", 33.1, 44.5, 48.2),
        ("MUX_S3", "16", "13", 32.4, 45.2, 48.9),
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
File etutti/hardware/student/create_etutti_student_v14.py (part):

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            route_2layer_clean(pmm[0], pmm[1], pu5[0], pu5[1], gx_mux, net_n, 0.20)

        # 6G. 28-KEY MATRIX ROUTING (Every single net has a globally unique X column in its vertical span!)
        # U4 Left Pins (KEY_SIG_1..8): 8 strictly distinct columns at X = 39.26, 38.58, 37.90, 37.22, 36.54, 35.86, 35.18, 34.50
        u4_left_gx  = [39.26 - i * 0.68 for i in range(8)]
        # U4 Right Pins (KEY_SIG_9..16): 8 strictly distinct columns at X = 50.30 + i * 0.68
        u4_right_gx = [50.30 + i * 0.68 for i in range(8)]
        # U5 Left Pins (KEY_SIG_17..24): 8 strictly distinct columns at X = 39.26, 38.58, 37.90, 37.22, 36.54, 35.86, 35.18, 34.50
        u5_left_gx  = [39.26 - i * 0.68 for i in range(8)]
        # U5 Right Pins (KEY_SIG_25..28): 4 strictly distinct columns at X = 50.30 + i * 0.68
        u5_right_gx = [50.30 + i * 0.68 for i in range(4)]

        for k in range(1, 29):
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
